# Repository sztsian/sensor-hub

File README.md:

# sensor-hub

This is an ESP8266 board with some connectors for sensors.

The board is made with Raspberry Pi 3 form factor so it can fit into a Raspberry Pi 3 B shell easily if you want.

# Hardware

The board itself is design in KiCAD. Note, I am not a profession in electronics, so the board can be error pron or unstable.

The kicad symbol of the button is from [this website](http://smisioto.no-ip.org/elettronica/kicad/kicad-en.htm). You need to download the package/symbol and config it in your KiCAD.

# Firmware

[Tasmota](https://github.com/arendst/Tasmota) fits me well for gathering the sensor information and send it via MQTT. You can either download one from Tasmota, or compile your own for your need.
The config I use for [TasmoCompiler](https://github.com/benzino77/tasmocompiler) docker based compiler is available as `firmware/tasmota-zigbee-ir-i2c-user_config_override.h` .

The following is the config I use for the first picture.

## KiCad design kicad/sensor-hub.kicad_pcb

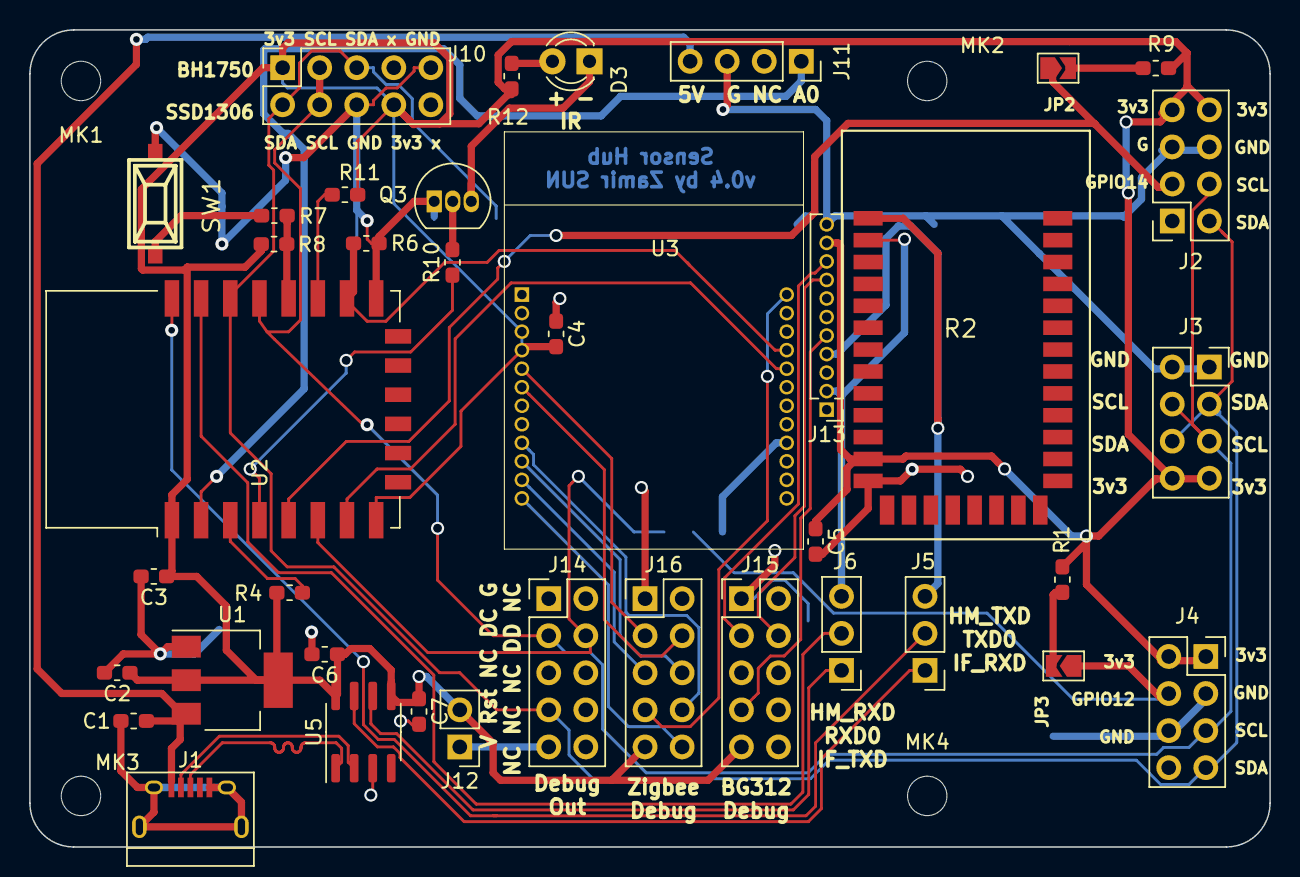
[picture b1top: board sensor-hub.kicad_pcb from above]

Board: 2 copper layers, 85.0 x 56.0 mm, 44 parts (1 on the bottom side), 41 nets.

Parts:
C1: 10uF; C_0603_1608Metric_Pad1.05x0.95mm_HandSolder
C2: 100uF; C_0603_1608Metric_Pad1.05x0.95mm_HandSolder
C3, C4, C5, C6, C7: 100nF; C_0603_1608Metric_Pad1.05x0.95mm_HandSolder
D3: Infrared; LED_D3.0mm_IRBlack
J1: USB_B_Micro; USB_Micro-B_Connector
J2: IO14/SHT; PinSocket_2x04_P2.54mm_Vertical
J3: HDC/Si7021; PinSocket_2x04_P2.54mm_Vertical
J4: IO12/SHT; PinSocket_2x04_P2.54mm_Vertical
J5: ESP_TXD; PinHeader_1x03_P2.54mm_Vertical
J6: ESP_RXD; PinHeader_1x03_P2.54mm_Vertical
J10: BH1750/Display; PinSocket_2x05_P2.54mm_Vertical
J11: MQ_Sensors; PinSocket_1x04_P2.54mm_Vertical
J12: CC_PWR; PinHeader_1x02_P2.54mm_Vertical
J13: BG312L; PinHeader_1x11_P1.27mm_Vertical
J14: CC_DBG; PinHeader_2x05_P2.54mm_Vertical
J15: BT_DBG; PinHeader_2x05_P2.54mm_Vertical
J16: ZB_DBG; PinHeader_2x05_P2.54mm_Vertical
JP1: SJ_DHT; SolderJumper-3_P2.0mm_Open_TrianglePad1.0x1.5mm
JP2: SJ_GPIO14; SolderJumper-2_P1.3mm_Open_TrianglePad1.0x1.5mm
JP3: SJ_GPIO12; SolderJumper-2_P1.3mm_Open_TrianglePad1.0x1.5mm
MK1, MK2, MK3, MK4: M2.5; MountingHole_2.7mm_M2.5
Q3: PN2222A; TO-92_Inline
R1, R9: 4.7k; R_0603_1608Metric_Pad1.05x0.95mm_HandSolder
R2: hm10; HM10
R4, R6, R8: 10k; R_0603_1608Metric_Pad1.05x0.95mm_HandSolder
R7: 470; R_0603_1608Metric_Pad1.05x0.95mm_HandSolder
R10: 2.7k; R_0603_1608Metric_Pad1.05x0.95mm_HandSolder
R11: R_Small; R_0603_1608Metric_Pad1.05x0.95mm_HandSolder
R12: 2.5R; R_0603_1608Metric_Pad1.05x0.95mm_HandSolder
SW1: SW_Flash; smd_push
U1: AP1117-33; SOT-223-3_TabPin2
U2: ESP-12F; ESP-12E
U3: SZ1-CC2530
U5: CH330N; SOIC-8_3.9x4.9mm_P1.27mm

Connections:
3V3_MCU: C2.1, C3.1, C4.2, C5.1, C6.1, C7.1, J2.7, J2.8, J3.7, J3.8, J4.1, J4.2, J10.1, J10.8, J12.2, J13.10, J15.9, J16.9, R1.1, R2.12, R4.2, R8.1, R9.1, R11.1, R12.2, U1.2, U2.1, U2.8, U3.3, U3.4, U5.5, U5.8
/ZB_07: JP1.3, U3.16
/ZB_CLK: J16.6, U3.10
/ZB_CS: J16.5, U3.11
/ZB_DC: J16.3, U3.5
/ZB_DD: J16.4, U3.6
/ZB_MISO: J16.10, U3.12
/ZB_MOSI: J16.8, U3.9
/ZB_RST: J16.7, U3.24
A0: J11.1, U2.2
BT_DC: J13.9, J15.3
BT_DD: J13.8, J15.4
BT_RST: J13.5, J15.7
DHT22: J4.4, JP1.2, JP3.1
GND: C1.2, C2.2, C3.2, C4.1, C5.2, C6.2, C7.2, J1.5, J1.6, J2.5, J2.6, J3.1, J3.2, J4.3, J4.6, J10.6, J10.9, J11.3, J13.1, J13.11, J14.1, J15.1, J16.1, Q3.1, R2.13, R6.1, SW1.2, U1.1, U2.15, U3.1, U3.2, U5.3
GPIO0: R7.2, R8.2, U2.18
GPIO2: R11.2, U2.17
GPIO4: J2.4, J3.4, J3.5, J4.5, J10.3, J10.4, J14.3, U2.19
GPIO5: J2.2, J3.3, J3.6, J4.7, J10.2, J10.5, J14.7, U2.20
GPIO12: J14.4, JP1.1, U2.6
GPIO13: U2.7, U3.20
GPIO14: J2.3, JP2.1, U2.5
GPIO15: R6.2, U2.16, U3.21
GPIO16: R10.1, U2.4
HM_RXD: J6.3, J13.2, R2.2
HM_TXD: J5.3, J13.4, R2.1
IF_RXD: J5.1, U5.7
IF_TXD: J6.1, U5.6
IR_M: D3.1, Q3.3
IR_P: D3.2, R12.1
unnamed: J12.1, J14.9
unnamed: JP2.2, R9.2
unnamed: JP3.2, R1.2
unnamed: Q3.2, R10.2
unnamed: R4.1, U2.3
unnamed: R7.1, SW1.1
RXD0: J6.2, U2.21
TXD0: J5.2, U2.22
USB-D+: J1.3, U5.1
USB-D-: J1.2, U5.2
VBUS: C1.1, J1.1, J11.4, U1.3

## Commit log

2020-06-25 Initial sensor-hub kicad files
2020-06-25 Add cad libraries
2020-06-25 Update kicad files
2020-06-25 Add README and firmware
2020-06-25 Add config reference
2021-01-05 WIP: v0.4 with pin order converter board
2021-01-05 Finalize v0.4 version without pin converter board
